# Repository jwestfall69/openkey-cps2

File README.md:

# openkey-cps2

* [Overview](#overview)
* [Project Status](#project-status)
* [Supported Games](#supported-games)
* [Hardware](#hardware)
   * [PCB Manufacturing](#pcb-manufacturing)
   * [BOM](#bom)
   * [Assembly](#assembly)
* [Programming](#programming)
  * [Hardware](#hardware-1)
  * [Software](#software)
  * [Testing](#testing)
* [Installation](#installation)
  * [93646B-3](#93646b-3)
  * [93646B-4](#93646b-4)
  * [93646B-5](#93646b-5)
  * [93646B-6](#93646b-6)
  * [93646B-7](#93646b-7)
  * [97691A-3 (all in one)](#97691a-3-all-in-one)
  * [97691A-4 (all in one)](#97691a-4-all-in-one)

## Overview
This is an opensource/hardware implementation of an on the fly CPS2 key programmer that consists of a board thats soldered onto the CPS2 B board or the CPS2 all-in-one boards.

**NOTE**: There is a typo on the silkscreen on hardware revision 2022-12-17.  The bypass cap is listed as being 100uf, when it should be 100nf.  This typo was fixed in hardware revision 2023-01-03, however the pictures below are all from the typo'd 2022-12-17 revision.

Individual boards:<br>

Panel:<br>

Details on *how* to program a CPS2 key data can be found in [Eduardo Cruz](http://arcadehacker.blogspot.com/)'s [write up](http://arcadehacker.blogspot.com/2016/09/capcom-cps2-security-programming-guide.html) and associated [firmware](https://github.com/ArcadeHacker/ArcadeHacker_CPS2).

Details on *what* to program can be found in MAME's [CPS2 driver](https://github.com/mamedev/mame/blob/master/src/mame/capcom/cps2.cpp) (the *.key files).

## Project Status
**PCB:** I would consider the design PCB done at this point.  I'm open to any input on changes/improvements as this is my first PCB design.

**Firmware:** Should be fulling working but more testing would be nice.  There are a lot of CPS2 games/keys.

**Documentation:** Work in progress

## Supported Games
**IMPORTANT**: You will want to program the ATtiny before soldering your game jumpers.  Specifically jumper #5 is also the programming pin on the ATtiny.  Jumping it will tie the pin to ground which will make programming impossible.

| Jumper<br>1234&nbsp;5678 | Program<br>ROM Labels | Mame<br>Rom Set | Game Names |
|:---------------:|:-------------|:------------|:-----------|
| 0000&nbsp;0000 | nffe | 1944 | 1944: The Loop Master (Euro 000620) |
| 0000 0001 | nffj | 1944j | 1944: The Loop Master (Japan 000620) |
| 0000 0010 | nffu | 1944u | 1944: The Loop Master (USA 000620) |
| 0000 0011 | 19xe | 19xx | 19XX: The War Against Destiny (Euro 960104) |
| 0000 0100 | 09xa<br>19xa | 19xxa<br>19xxar1 | 19XX: The War Against Destiny (Asia 960104)<br>19XX: The War Against Destiny (Asia 951207) |
| 0000 0101 | 19xb | 19xxb | 19XX: The War Against Destiny (Brazil 951218) |
| 0000 0110 | 19xh | 19xxh | 19XX: The War Against Destiny (Hispanic 951218) |
| 0000 0111 | 19xj-03b<br>19xj<br>19xj | 19xxj<br>19xxjr1<br>19xxjr2 | 19XX: The War Against Destiny (Japan 960104, yellow case)<br>19XX: The War Against Destiny (Japan 951225)<br>19XX: The War Against Destiny (Japan 951207) |
| 0000 1000 | 19xu | 19xxu | 19XX: The War Against Destiny (USA 951207) |
| 0000 1001 | pwge<br>pwge | armwar<br>armwarr1 | Armored Warriors (Euro 941024)<br>Armored Warriors (Euro 941011) |
| 0000 1010 | pwga<br>pwga | armwara<br>armwarar1 | Armored Warriors (Asia 941024)<br>Armored Warriors (Asia 940920) |
| 0000 1011 | pwgb | armwarb | Armored Warriors (Brazil 941024) |
| 0000 1100 | pwgu<br>pwgu | armwaru<br>armwaru1 | Armored Warriors (USA 941024)<br>Armored Warriors (USA 940920) |
| 0000 1101 | avpe | avsp | Alien vs. Predator (Euro 940520) |
| 0000 1110 | avpa | avspa | Alien vs. Predator (Asia 940520) |
| 0000 1111 | avph | avsph | Alien vs. Predator (Hispanic 940520) |
| 0001 0000 | avpj | avspj | Alien vs. Predator (Japan 940520) |
| 0001 0001 | avpu | avspu | Alien vs. Predator (USA 940520) |
| 0001 0010 | btce | batcir | Battle Circuit (Euro 970319) |
| 0001 0011 | btca | batcira | Battle Circuit (Asia 970319) |
| 0001 0100 | btcj | batcirj | Battle Circuit (Japan 970319) |
| 0001 0101 | tkoj | choko | Janpai Puzzle Choukou (Japan 010820) |
| 0001 0110 | csce<br>csce | csclub<br>csclub1 | Capcom Sports Club (Euro 971017)<br>Capcom Sports Club (Euro 970722) |
| 0001 0111 | csca | cscluba | Capcom Sports Club (Asia 970722) |
| 0001 1000 | csch | csclubh | Capcom Sports Club (Hispanic 970722) |
| 0001 1001 | cscj<br>cscj | csclubj<br>csclubjy | Capcom Sports Club (Japan 970722)<br>Capcom Sports Club (Japan 970722, yellow case) |
| 0001 1010 | cybe | cybots | Cyberbots: Fullmetal Madness (Euro 950424) |
| 0001 1011 | cybj | cybotsj | Cyberbots: Fullmetal Madness (Japan 950420) |
| 0001 1100 | cybu | cybotsu | Cyberbots: Fullmetal Madness (USA 950424) |
| 0001 1101 | dd2e<br>dd2e<br>dd2e<br>dd2e | ddsom<br>ddsomr1<br>ddsomr2<br>ddsomr3 | Dungeons & Dragons: Shadow over Mystara (Euro 960619)<br>Dungeons & Dragons: Shadow over Mystara (Euro 960223)<br>Dungeons & Dragons: Shadow over Mystara (Euro 960209)<br>Dungeons & Dragons: Shadow over Mystara (Euro 960208) |
| 0001 1110 | dd2a<br>dd2a | ddsoma<br>ddsomar1 | Dungeons & Dragons: Shadow over Mystara (Asia 960619)<br>Dungeons & Dragons: Shadow over Mystara (Asia 960208) |
| 0001 1111 | dd2b | ddsomb | Dungeons & Dragons: Shadow over Mystara (Brazil 960223) |
| 0010 0000 | dd2h | ddsomh | Dungeons & Dragons: Shadow over Mystara (Hispanic 960223) |
| 0010 0001 | dd2j<br>dd2j<br>dd2j | ddsomj<br>ddsomjr1<br>ddsomjr2 | Dungeons & Dragons: Shadow over Mystara (Japan 960619)<br>Dungeons & Dragons: Shadow over Mystara (Japan 960206)<br>Dungeons & Dragons: Shadow over Mystara (Japan 960223) |
| 0010 0010 | dd2u<br>dd2u | ddsomu<br>ddsomur1 | Dungeons & Dragons: Shadow over Mystara (USA 960619)<br>Dungeons & Dragons: Shadow over Mystara (USA 960209) |
| 0010 0011 | dade<br>dade | ddtod<br>ddtodr1 | Dungeons & Dragons: Tower of Doom (Euro 940412)<br>Dungeons & Dragons: Tower of Doom (Euro 940113) |
| 0010 0100 | dada<br>dada | ddtoda<br>ddtodar1 | Dungeons & Dragons: Tower of Doom (Asia 940412)<br>Dungeons & Dragons: Tower of Doom (Asia 940113) |
| 0010 0101 | dadh<br>dadh<br>dadh | ddtodh<br>ddtodhr1<br>ddtodhr2 | Dungeons & Dragons: Tower of Doom (Hispanic 940412)<br>Dungeons & Dragons: Tower of Doom (Hispanic 940125)<br>Dungeons & Dragons: Tower of Doom (Hispanic 940113) |
| 0010 0110 | dadj<br>dadj<br>dadj | ddtodj<br>ddtodjr1<br>ddtodjr2 | Dungeons & Dragons: Tower of Doom (Japan 940412)<br>Dungeons & Dragons: Tower of Doom (Japan 940125)<br>Dungeons & Dragons: Tower of Doom (Japan 940113) |
| 0010 0111 | dadu<br>dadu | ddtodu<br>ddtodur1 | Dungeons & Dragons: Tower of Doom (USA 940125)<br>Dungeons & Dragons: Tower of Doom (USA 940113) |
| 0010 1000 | gmde | dimahoo | Dimahoo (Euro 000121) |
| 0010 1001 | gmdu | dimahoou | Dimahoo (USA 000121) |
| 0010 1010 | vame | dstlk | Darkstalkers: The Night Warriors (Euro 940705) |
| 0010 1011 | vama | dstlka | Darkstalkers: The Night Warriors (Asia 940705) |
| 0010 1100 | vamh | dstlkh | Darkstalkers: The Night Warriors (Hispanic 940818) |
| 0010 1101 | vamu<br>vamu | dstlku<br>dstlkur1 | Darkstalkers: The Night Warriors (USA 940818)<br>Darkstalkers: The Night Warriors (USA 940705) |
| 0010 1110 | uece | ecofghtr | Eco Fighters (World 931203) |
| 0010 1111 | ueca | ecofghtra | Eco Fighters (Asia 931203) |
| 0011 0000 | uech | ecofghtrh | Eco Fighters (Hispanic 931203) |
| 0011 0001 | uecu<br>uecu | ecofghtru<br>ecofghtru1 | Eco Fighters (USA 940215)<br>Eco Fighters (USA 931203) |
| 0011 0010 | ggwu | gigawing | Giga Wing (USA 990222) |
| 0011 0011 | ggwa | gigawinga | Giga Wing (Asia 990222) |
| 0011 0100 | ggwb | gigawingb | Giga Wing (Brazil 990222) |
| 0011 0101 | ggwh | gigawingh | Giga Wing (Hispanic 990222) |
| 0011 0110 | ggwj | gigawingj | Giga Wing (Japan 990223) |
| 0011 0111 | gmdj | gmahou | Great Mahou Daisakusen (Japan 000121) |
| 0011 1000 | hs2u | hsf2 | Hyper Street Fighter II: The Anniversary Edition (USA 040202) |
| 0011 1001 | hs2a | hsf2a | Hyper Street Fighter II: The Anniversary Edition (Asia 040202) |
| 0011 1010 | hs2j<br>hs2j | hsf2j<br>hsf2j1<br>hsf2j2 | Hyper Street Fighter II: The Anniversary Edition (Japan 040202)<br>Street Fighter II: The Anniversary Edition (Japan 040123)<br>Hyper Street Fighter II: The Anniversary Edition (Japan 031222) |
| 0011 1011 | majj | jyangoku | Jyangokushi: Haoh no Saihai (Japan 990527) |
| 0011 1100 | rm2u | megaman2 | Mega Man 2: The Power Fighters (USA 960708) |
| 0011 1101 | rm2a | megaman2a | Mega Man 2: The Power Fighters (Asia 960708) |
| 0011 1110 | rm2h | megaman2h | Mega Man 2: The Power Fighters (Hispanic 960712) |
| 0011 1111 | rcmu<br>rcmu<br>rcmu | mmancp2u<br>mmancp2ur1<br>mmancp2ur2 | Mega Man: The Power Battle (CPS2, USA 951006, SAMPLE Version)<br>Mega Man: The Power Battle (CPS2, USA 950926, SAMPLE Version)<br>Mega Man: The Power Battle (CPS2, USA 950925, SAMPLE Version) |
| 0100 0000 | sys_rom1 | mmatrix | Mars Matrix: Hyper Solid Shooting (USA 000412) |
| 0100 0001 | mmxa | mmatrixa | Mars Matrix: Hyper Solid Shooting (Asia 000412) |
| 0100 0010 | mmxj | mmatrixj | Mars Matrix: Hyper Solid Shooting (Japan 000412) |
| 0100 0011 | mpne<br>mpn_03a<br>mpnj<br>mpne<br>mpnu | mpang<br>mpanga<br>mpangj<br>mpangr1<br>mpangu | Mighty! Pang (Euro 001010)<br>Mighty! Pang (Asia 001010)<br>Mighty! Pang (Japan 001011)<br>Mighty! Pang (Euro 000925)<br>Mighty! Pang (USA 001010) |
| 0100 0100 | mshe | msh | Marvel Super Heroes (Euro 951024) |
| 0100 0101 | msha | msha | Marvel Super Heroes (Asia 951024) |
| 0100 0110 | mshb<br>mshb | mshb<br>mshbr1 | Marvel Super Heroes (Brazil 951117)<br>Marvel Super Heroes (Brazil 951024) |
| 0100 0111 | mshh | mshh | Marvel Super Heroes (Hispanic 951117) |
| 0100 1000 | mshj<br>mshj | mshj<br>mshjr1 | Marvel Super Heroes (Japan 951117)<br>Marvel Super Heroes (Japan 951024) |
| 0100 1001 | mshu | mshu | Marvel Super Heroes (USA 951024) |
| 0100 1010 | mvse | mshvsf | Marvel Super Heroes Vs. Street Fighter (Euro 970625) |
| 0100 1011 | mvsa<br>mvsa | mshvsfa<br>mshvsfa1 | Marvel Super Heroes Vs. Street Fighter (Asia 970625)<br>Marvel Super Heroes Vs. Street Fighter (Asia 970620) |
| 0100 1100 | mvsb<br>mvsb | mshvsfb<br>mshvsfb1 | Marvel Super Heroes Vs. Street Fighter (Brazil 970827)<br>Marvel Super Heroes Vs. Street Fighter (Brazil 970625) |
| 0100 1101 | mvsh | mshvsfh | Marvel Super Heroes Vs. Street Fighter (Hispanic 970625) |
| 0100 1110 | mvsj<br>mvsj<br>mvsj | mshvsfj<br>mshvsfj1<br>mshvsfj2 | Marvel Super Heroes Vs. Street Fighter (Japan 970707)<br>Marvel Super Heroes Vs. Street Fighter (Japan 970702)<br>Marvel Super Heroes Vs. Street Fighter (Japan 970625) |
| 0100 1111 | mvsu<br>mvsu | mshvsfu<br>mshvsfu1 | Marvel Super Heroes Vs. Street Fighter (USA 970827)<br>Marvel Super Heroes Vs. Street Fighter (USA 970625) |
| 0101 0000 | mvce<br>mvce | mvsc<br>mvscr1 | Marvel Vs. Capcom: Clash of Super Heroes (Euro 980123)<br>Marvel Vs. Capcom: Clash of Super Heroes (Euro 980112) |
| 0101 0001 | mvca<br>mvca | mvsca<br>mvscar1 | Marvel Vs. Capcom: Clash of Super Heroes (Asia 980123)<br>Marvel Vs. Capcom: Clash of Super Heroes (Asia 980112) |
| 0101 0010 | mvcb | mvscb | Marvel Vs. Capcom: Clash of Super Heroes (Brazil 980123) |
| 0101 0011 | mvch | mvsch | Marvel Vs. Capcom: Clash of Super Heroes (Hispanic 980123) |
| 0101 0100 | mvcj<br>mvcj<br>mvc_ja | mvscj<br>mvscjr1<br>mvscjsing | Marvel Vs. Capcom: Clash of Super Heroes (Japan 980123)<br>Marvel Vs. Capcom: Clash of Super Heroes (Japan 980112)<br>Marvel Vs. Capcom: Clash of Super Heroes (Japan 980123) (Single PCB) |
| 0101 0101 | mvcu<br>mvcu | mvscu<br>mvscur1 | Marvel Vs. Capcom: Clash of Super Heroes (USA 980123)<br>Marvel Vs. Capcom: Clash of Super Heroes (USA 971222) |
| 0101 0110 | vphe | nwarr | Night Warriors: Darkstalkers' Revenge (Euro 950316) |
| 0101 0111 | vpha | nwarra | Night Warriors: Darkstalkers' Revenge (Asia 950302) |
| 0101 1000 | vphb | nwarrb | Night Warriors: Darkstalkers' Revenge (Brazil 950403) |
| 0101 1001 | vphh | nwarrh | Night Warriors: Darkstalkers' Revenge (Hispanic 950403) |
| 0101 1010 | vphu | nwarru | Night Warriors: Darkstalkers' Revenge (USA 950406) |
| 0101 1011 | pcfj | pfghtj | Pocket Fighter (Japan 970904) |
| 0101 1100 | pwgj<br>pwgj | pgear<br>pgearr1 | Powered Gear: Strategic Variant Armor Equipment (Japan 941024)<br>Powered Gear: Strategic Variant Armor Equipment (Japan 940916) |
| 0101 1101 | pgau | progear | Progear (USA 010117) |
| 0101 1110 | pgaa | progeara | Progear (Asia 010117) |
| 0101 1111 | pgaj | progearj | Progear no Arashi (Japan 010117) |
| 0110 0000 | pl2e<br>pl2j<br>pl2j | pzloop2<br>pzloop2j<br>pzloop2jr1 | Puzz Loop 2 (Euro 010302)<br>Puzz Loop 2 (Japan 010226)<br>Puzz Loop 2 (Japan 010205) |
| 0110 0001 | tqzj | qndream | Quiz Nanairo Dreams: Nijiirochou no Kiseki (Japan 96086) |
| 0110 0010 | smbe | ringdest | Ring of Destruction: Slammasters II (Euro 940902) |
| 0110 0011 | smba | ringdesta | Ring of Destruction: Slammasters II (Asia 940831) |
| 0110 0100 | smbb<br>smbh | ringdestb<br>ringdesth | Ring of Destruction: Slammasters II (Brazil 940902)<br>Ring of Destruction: Slammasters II (Hispanic 940902) |
| 0110 0101 | rcmj | rmancp2j | Rockman: The Power Battle (CPS2, Japan 950922) |
| 0110 0110 | rm2j | rockman2j | Rockman 2: The Power Fighters (Japan 960708) |
| 0110 0111 | sfze<br>sfze<br>sfze<br>sfze | sfa<br>sfar1<br>sfar2<br>sfar3 | Street Fighter Alpha: Warriors' Dreams (Euro 950727)<br>Street Fighter Alpha: Warriors' Dreams (Euro 950718)<br>Street Fighter Alpha: Warriors' Dreams (Euro 950627)<br>Street Fighter Alpha: Warriors' Dreams (Euro 950605) |
| 0110 1000 | sz2e | sfa2 | Street Fighter Alpha 2 (Euro 960229) |
| 0110 1001 | sz2u<br>sz2u | sfa2u<br>sfa2ur1 | Street Fighter Alpha 2 (USA 960430)<br>Street Fighter Alpha 2 (USA 960306) |
| 0110 1010 | sz3e | sfa3 | Street Fighter Alpha 3 (Euro 980904) |
| 0110 1011 | sz3b | sfa3b | Street Fighter Alpha 3 (Brazil 980629) |
| 0110 1100 | sz3h<br>sz3h | sfa3h<br>sfa3hr1 | Street Fighter Alpha 3 (Hispanic 980904)<br>Street Fighter Alpha 3 (Hispanic 980629) |
| 0110 1101 | sz3u<br>sz3u<br>sz3-usam_03 | sfa3u<br>sfa3ur1<br>sfa3us | Street Fighter Alpha 3 (USA 980904)<br>Street Fighter Alpha 3 (USA 980629)<br>Street Fighter Alpha 3 (USA 980616, SAMPLE Version) |
| 0110 1110 | sfzu | sfau | Street Fighter Alpha: Warriors' Dreams (USA 950627) |
| 0110 1111 | sz2a | sfz2a | Street Fighter Zero 2 (Asia 960227) |
| 0111 0000 | szaa<br>szaa | sfz2al<br>sfz2alr1 | Street Fighter Zero 2 Alpha (Asia 960826)<br>Street Fighter Zero 2 Alpha (Asia 960805) |
| 0111 0001 | szab | sfz2alb | Street Fighter Zero 2 Alpha (Brazil 960813) |
| 0111 0010 | szah | sfz2alh | Street Fighter Zero 2 Alpha (Hispanic 960813) |
| 0111 0011 | szaj | sfz2alj | Street Fighter Zero 2 Alpha (Japan 960805) |
| 0111 0100 | sz2b<br>sz2b | sfz2b<br>sfz2br1 | Street Fighter Zero 2 (Brazil 960531)<br>Street Fighter Zero 2 (Brazil 960304) |
| 0111 0101 | sz2h | sfz2h | Street Fighter Zero 2 (Hispanic 960304) |
| 0111 0110 | sz2j<br>sz2j | sfz2j<br>sfz2jr1 | Street Fighter Zero 2 (Japan 960430)<br>Street Fighter Zero 2 (Japan 960227) |
| 0111 0111 | sz2n | sfz2n | Street Fighter Zero 2 (Oceania 960229) |
| 0111 1000 | sz3a<br>sz3a | sfz3a<br>sfz3ar1 | Street Fighter Zero 3 (Asia 980904)<br>Street Fighter Zero 3 (Asia 980701) |
| 0111 1001 | sz3j<br>sz3j<br>sz3j | sfz3j<br>sfz3jr1<br>sfz3jr2 | Street Fighter Zero 3 (Japan 980904)<br>Street Fighter Zero 3 (Japan 980727)<br>Street Fighter Zero 3 (Japan 980629) |
| 0111 1010 | sfza<br>sfza | sfza<br>sfzar1 | Street Fighter Zero (Asia 950627)<br>Street Fighter Zero (Asia 950605) |
| 0111 1011 | sfzb<br>sfzb | sfzb<br>sfzbr1 | Street Fighter Zero (Brazil 951109)<br>Street Fighter Zero (Brazil 950727) |
| 0111 1100 | sfzh<br>sfzh | sfzh<br>sfzhr1 | Street Fighter Zero (Hispanic 950718)<br>Street Fighter Zero (Hispanic 950627) |
| 0111 1101 | sfzj<br>sfzj<br>sfzj | sfzj<br>sfzjr1<br>sfzjr2 | Street Fighter Zero (Japan 950727)<br>Street Fighter Zero (Japan 950627)<br>Street Fighter Zero (Japan 950605) |
| 0111 1110 | pcfu | sgemf | Super Gem Fighter Mini Mix (USA 970904) |
| 0111 1111 | pcfa | sgemfa | Super Gem Fighter: Mini Mix (Asia 970904) |
| 1000 0000 | pcfh | sgemfh | Super Gem Fighter: Mini Mix (Hispanic 970904) |
| 1000 0001 | smbj<br>smbj | smbomb<br>smbombr1 | Super Muscle Bomber: The International Blowout (Japan 940831)<br>Super Muscle Bomber: The International Blowout (Japan 940808) |
| 1000 0010 | pzfe | spf2t | Super Puzzle Fighter II Turbo (Euro 960529) |
| 1000 0011 | pzfa | spf2ta | Super Puzzle Fighter II Turbo (Asia 960529) |
| 1000 0100 | pzfh | spf2th | Super Puzzle Fighter II Turbo (Hispanic 960531) |
| 1000 0101 | pzfu | spf2tu | Super Puzzle Fighter II Turbo (USA 960620) |
| 1000 0110 | pzfj | spf2xj | Super Puzzle Fighter II X (Japan 960531) |
| 1000 0111 | ssfe<br>ssfe | ssf2<br>ssf2r1 | Super Street Fighter II: The New Challengers (World 931005)<br>Super Street Fighter II: The New Challengers (World 930911) |
| 1000 1000 | ssfa<br>ssfa | ssf2a<br>ssf2ar1 | Super Street Fighter II: The New Challengers (Asia 931005)<br>Super Street Fighter II: The New Challengers (Asia 930914) |
| 1000 1001 | ssfh | ssf2h | Super Street Fighter II: The New Challengers (Hispanic 930911) |
| 1000 1010 | ssfj<br>ssfj<br>ssfj | ssf2j<br>ssf2jr1<br>ssf2jr2 | Super Street Fighter II: The New Challengers (Japan 931005)<br>Super Street Fighter II: The New Challengers (Japan 930911)<br>Super Street Fighter II: The New Challengers (Japan 930910) |
| 1000 1011 | ssfh | ssf2t | Super Street Fighter II Turbo (World 940223) |
| 1000 1100 | sfxa | ssf2ta | Super Street Fighter II Turbo (Asia 940223) |
| 1000 1101 | ssfe<br>ssfe | ssf2tb<br>ssf2tbr1 | Super Street Fighter II: The Tournament Battle (World 931119)<br>Super Street Fighter II: The Tournament Battle (World 930911) |
| 1000 1110 | ssfa | ssf2tba | Super Street Fighter II: The Tournament Battle (Asia 931005) |
| 1001 0000 | ssftj<br>ssfj | ssf2tbj<br>ssf2tbj1 | Super Street Fighter II: The Tournament Battle (Japan 931005)<br>Super Street Fighter II: The Tournament Battle (Japan 930911) |
| 1001 0001 | ssfu | ssf2tbu | Super Street Fighter II: The Tournament Battle (USA 930911) |
| 1001 0010 | sfxh | ssf2th | Super Street Fighter II Turbo (Hispanic 940223) |
| 1001 0011 | sfxu<br>sfxu | ssf2tu<br>ssf2tur1 | Super Street Fighter II Turbo (USA 940323)<br>Super Street Fighter II Turbo (USA 940223) |
| 1001 0100 | ssfu<br>ssfu | ssf2u<br>ssf2us2 | Super Street Fighter II: The New Challengers (USA 930911)<br> |
| 1001 0101 | sfxj<br>sfxj | ssf2xj<br>ssf2xjr1 | Super Street Fighter II X: Grand Master Challenge (Japan 940311)<br>Super Street Fighter II X: Grand Master Challenge (Japan 940223) |
| 1001 0110 | sfxo | ssf2xjr1r | Super Street Fighter II X: Grand Master Challenge (Japan 940223 rent version) |
| 1001 0111 | uecj | uecology | Ultimate Ecology (Japan 931203) |
| 1001 1000 | vamj<br>vamj<br>vamj | vampj<br>vampja<br>vampjr1 | Vampire: The Night Warriors (Japan 940705)<br>Vampire: The Night Warriors (Japan 940705 alt)<br>Vampire: The Night Warriors (Japan 940630) |
| 1001 1001 | vh2j<br>vh2j | vhunt2<br>vhunt2r1 | Vampire Hunter 2: Darkstalkers Revenge (Japan 970929)<br>Vampire Hunter 2: Darkstalkers Revenge (Japan 970913) |
| 1001 1010 | vphj<br>vphj<br>vphjstop<br>vphj | vhuntj<br>vhuntjr1<br>vhuntjr1s<br>vhuntjr2 | Vampire Hunter: Darkstalkers' Revenge (Japan 950316)<br>Vampire Hunter: Darkstalkers' Revenge (Japan 950307)<br>Vampire Hunter: Darkstalkers' Revenge (Japan 950307 stop version)<br>Vampire Hunter: Darkstalkers' Revenge (Japan 950302) |
| 1001 1011 | vm3e | vsav | Vampire Savior: The Lord of Vampire (Euro 970519) |
| 1001 1100 | vs2j | vsav2 | Vampire Savior 2: The Lord of Vampire (Japan 970913) |
| 1001 1101 | vm3a | vsava | Vampire Savior: The Lord of Vampire (Asia 970519) |
| 1001 1110 | vm3b | vsavb | Vampire Savior: The Lord of Vampire (Brazil 970519) |
| 1001 1111 | vm3h | vsavh | Vampire Savior: The Lord of Vampire (Hispanic 970519) |
| 1010 0000 | vm3j | vsavj | Vampire Savior: The Lord of Vampire (Japan 970519) |
| 1010 0001 | vm3u | vsavu | Vampire Savior: The Lord of Vampire (USA 970519) |
| 1010 0010 | xmne<br>xmne | xmcota<br>xmcotar1 | X-Men: Children of the Atom (Euro 950331)<br>X-Men: Children of the Atom (Euro 950105) |
| 1010 0011 | xmna<br>xmna<br>xmna | xmcotaa<br>xmcotaar1<br>xmcotaar2 | X-Men: Children of the Atom (Asia 950105)<br>X-Men: Children of the Atom (Asia 941219)<br>X-Men: Children of the Atom (Asia 941217) |
| 1010 0100 | xmnb | xmcotab | X-Men: Children of the Atom (Brazil 950331) |
| 1010 0101 | xmnh<br>xmnh | xmcotah<br>xmcotahr1 | X-Men: Children of the Atom (Hispanic 950331)<br>X-Men: Children of the Atom (Hispanic 950105) |
| 1010 0110 | xmnj<br>xmnj<br>xmnj<br>xmnj<br>xmno | xmcotaj<br>xmcotaj1<br>xmcotaj2<br>xmcotaj3<br>xmcotajr | X-Men: Children of the Atom (Japan 950105)<br>X-Men: Children of the Atom (Japan 941222)<br>X-Men: Children of the Atom (Japan 941219)<br>X-Men: Children of the Atom (Japan 941217)<br>X-Men: Children of the Atom (Japan 941208 rent version) |
| 1010 0111 | xmnu | xmcotau | X-Men: Children of the Atom (USA 950105) |
| 1010 1000 | xvse<br>xvse | xmvsf<br>xmvsfr1 | X-Men Vs. Street Fighter (Euro 961004)<br>X-Men Vs. Street Fighter (Euro 960910) |
| 1010 1001 | xvsa<br>xvsa<br>xvsa<br>xvsa | xmvsfa<br>xmvsfar1<br>xmvsfar2<br>xmvsfar3 | X-Men Vs. Street Fighter (Asia 961023)<br>X-Men Vs. Street Fighter (Asia 961004)<br>X-Men Vs. Street Fighter (Asia 960919)<br>X-Men Vs. Street Fighter (Asia 960910) |
| 1010 1010 | xvsb | xmvsfb | X-Men Vs. Street Fighter (Brazil 961023) |
| 1010 1011 | xvsh | xmvsfh | X-Men Vs. Street Fighter (Hispanic 961004) |
| 1010 1100 | xvsj<br>xvsj<br>xvsj<br>xvsj | xmvsfj<br>xmvsfjr1<br>xmvsfjr2<br>xmvsfjr3<br>xmvsfjr4 | X-Men Vs. Street Fighter (Japan 970113)<br>X-Men Vs. Street Fighter (Japan 961023)<br>X-Men Vs. Street Fighter (Japan 961004)<br>X-Men Vs. Street Fighter (Japan 960910)<br>X-Men Vs. Street Fighter (Japan 960909) |
| 1010 1101 | xvsu<br>xvsu<br>xvsu | xmvsfu<br>xmvsfur1<br>xmvsfur2 | X-Men Vs. Street Fighter (USA 961023)<br>X-Men Vs. Street Fighter (USA 961004)<br>X-Men Vs. Street Fighter (USA 960910) |
| 1010 1110 | | | Phoenix Key (0xff filled) |

## Hardware
### PCB Manufacturing
For thickness I've been using 1mm, but standard 1.6mm will work fine too.

The board has 2 sets of castellated holes (through holes cut in half on the edge of the board).  When ordering make sure you pick the option for castellated holes as they require special processing.  If you don't pick the option, your castellated holes will likely be mangled and look like this

**Mangled Castellated Holes**<br>

I've been using [jlcpcb](https://jlcpcb.com/) for PCB manufacturing.  For them, picking castellated holes adds around a $40 fee to the order.  They also seem to have an unwritten limit of 30 PCBs per order that have castellated holes.  If you go above this they may reject your order or ask you if its ok to remove the castellated holes option (don't do it!).

If you want more then 30 PCBs or want them assembled you will want to use the
panel version of openkey-cps2.  More detail regarding this can be found in [PANEL.md](PANEL.md).

### BOM
| Description | Part Number | DigiKey | Mouser | Notes |
|-------------|-------------|---------|--------|-------|
| ATtiny404 20Mhz | ATTINY404-SSN | [ATTINY404-SSN-ND](https://www.digikey.com/en/products/detail/microchip-technology/ATTINY404-SSN/9947546) | [556-ATTINY404-SSNR](https://www.mouser.com/ProductDetail/Microchip-Technology-Atmel/ATTINY404-SSNR?qs=F5EMLAvA7IAEqD7Aw0z%252B9Q%3D%3D) | Other ATtiny tinyAVR 0/1/2-series models should be viable as well.  The code compiles to a little over 3K in size, so any that have 4K or more of flash should work.  Just note I have only tested with 404s |
| 100nf / 0.1uf SMD Ceramic Capacitor 0805 Size | | | | |

### Assembly
Nothing special here just install the ATtiny and the bypass cap.

**IMPORTANT**: You will want to program the ATtiny before soldering your game jumpers.  Specifically jumper #5 is also the programming pin on the ATtiny.  Jumping it will tie the pin to ground which will make programming impossible.

## Programming
### Hardware
Programming is done with a UPDI programmer.  I've been using this one:

[Serial UPDI Programmer for ATmega 0-Series, or ATtiny 0-Series or 1-Series, or AVR DA or AVR DB](https://www.amazon.com/dp/B09X64YRLD?psc=1&ref=ppx_yo2ov_dt_b_product_details)

Note: This programmer (and likely others) has a switch for 3.3V and 5V.  Set it to 5V.

The openkey-cps2 programming port consists of 3x pads (VCC, GND, UPDI) that will need to be connected to the programmer.  I've been using a short 3 pin female to female IDC cable with [pogo pins](https://www.amazon.com/dp/B00X7C8PGE?psc=1&ref=ppx_yo2ov_dt_b_product_details) on one end to do this.  Additionally you could probably use something like [this](https://www.amazon.com/dp/B09MGG4C6X?ref=ppx_yo2ov_dt_b_product_details&th=1) if you are going to be programming a bunch.

Of course be sure you properly orient the board so the labeled pads match up.  vcc to vcc, gnd to gnd, and updi to updi.

### Software
For software I've been using the [Arduino IDE](https://www.arduino.cc/en/software/OldSoftwareReleases) with [megaTinyCore](https://github.com/SpenceKonde/megaTinyCore), which adds support for tinyAVR 0/1/2-Series MCUs.

**NOTE**: The makers of megaTinyCore currently recommend using Arduino IDE version 1.8.13 for best compatibility.
 2.0 definitely does not work!

To install the megaTinyCore you, should just need to add http://drazzy.com/package_drazzy.com_index.json to "Addit
ional Boards Manager URLs" in the settings for the Arduino IDE.

From there you need to configure the board/programming settings.  I've been using these:

### Testing
If you are selling or giving away the openkey-cps2's that you have assembled/programmed its nice to be able to test them first.  This section explains how you can test the board without having to install it.

You will need to get your hands on a "1944: The Loop Master (Euro 000620)" in a 93646B-6 or 93646B-7 B board.  For mine I just made a conversion using the 1944 mame romset.  This specific game is needed because its game jumper 0000 0000.

Additionally you will need to create the following cable

Side A:<br>

Side B:<br>

I would advise making this cable about 24 inches long.

You will note that side "A" is 6 pin female connectors, which break out into a 5 pin female connector and 3 pin female connector "B" side.  The "B" side then has pogo pins installed with super glue to keep them steady.  Additionally on the 3 pin female connector "B" side, pins 2 and 3 are just connected to each other.

The red wire is +5V, black wire is GND, remaining are data lines.

The "A" side 6 pin connector should be plugged into CN9 on the B board, with +5V on pin 1, and GND on pin 6 as shown.

**IMPORTANT**: The +5V on the 3 pin female/pogo pin connector will be live when you power on the board, so be extra careful you don't touch anything with it or it could cause a short/damage.

CPS2 boards will hold onto the programmed key data for a while after they have been powered off.  So to properly test the openkey-cps2 its best to program the wrong key, verify it breaks the game, then program the correct key to verify it works.

**Programming the WRONG key**
1. Power on the CPS2 board
2. Connect the 5 pogo pin connector to pins 2-6 of CN9 on the openkey-cps2
3. Connect the 3 pogo pin connector to the UPDI header on openkey-cps2, with the red wire connected to VCC pad, and the pins 2-3 connected to GND and UPDI pads

This should result is a solid color screen, mine is normally purple.

The UPDI pad on the UPDI header is shared with jumper #5 of the game select.  By jumping the GND and UPDI pads together its cause the MCU to program game 0000 1000 or 19XX: The War Against Destiny (USA 951207), which is the wrong key for 1944: The Loop Master (Euro 000620)

**Programming the CORRECT key**
1. Remove both the 5 pogo pin and 3 pogo pin connectors from the openkey-cps2 board
2. Connect the 5 pogo pin connector to pins 2-6 of CN9 on the openkey-cps2
3. Using the 3 pogo pin connector, only connect the red wire pogo pin to the VCC pad on the UPDI header.  Do not connect anything to the GND and UPDI pads

By only applying +5V on the VCC pad on UPDI header and NOT jumping the GND/UPDI pads it will cause the MCU to program game 0000 0000.

The game should boot a few seconds later

You do not need to power off the CPS2 board in between programming the wrong/correct key or even between testing multiple openkey-cps2 board.  Part of the programming process will reset the game.

## Installation
Below are pictures for installing openkey-cps2 on the different cps2 board revisions.  

You will notice there are 3 boxes on the board, 2 with solder pads (+5V and GND), and 1 jumper.  Within the box is a short hand version of which board revisions need which of them.

  * +5V has **B-345** which means its needed for revisions 93646**B-3**, 93646**B-4**, and 93646**B-5**
  * JUMP has **B-67** and **A-34** which means it needs to be jumped for revisions 93646**B-6**, 93646**B-7**, 97691**A-3** and 97691**A-4**
  * GND has **B-34** which means its needed for revisions 93646**B-3** and 93646**B-4**

### **93646B-3**
### **93646B-4**
---
93646B-3 and 93646B-4 have the same install process.

Identify CN2 on the top side of the CPS2 B Board PCB.  This is where openkey-cps2 will be installed.

Your board will likely have the resistor shown in the below picture.

Temporarily desolder the top connection of the resistor, move it out of the way and install openkey-cps2 as shown below.  Additionally make note of the red and green arrows/lines as these will be the locations we wire up for +5V and GND.

Re-solder the resistor and wire up the +5V and GND wires as shown below.  Then jumper 1 to 8 based on which game you need. 

### **93646B-5**
---
NOTE: I don't have a 93646B-5, but this is what should be required for the installation.

Identify CN9 on the top side of the CPS2 B Board PCB.  The underside of CN9 is what we will be installing openkey-cps2 to.

Top:

Bottom:

Solder the castellated holes on CN9 of openkey-cps2 to the underside pins for CN9 on the CPS2 PCB.  Additionally solder a wire going from the +5V pad on the openkey-cps2 to RA2 pin 1 as seen below.  Then jumper 1 to 8 based on which game you need.  

Installed:

### **93646B-6**
### **93646B-7**
---
93646B-6 and 93646B-7 have the same install process.

Identify CN9 on the top side of the CPS2 B Board PCB.  The underside of CN9 is what we will be installing openkey-cps2 to.

Top:

Bottom:

Solder the castellated holes on CN9 of openkey-cps2 to the underside pins for CN9 on the CPS2 PCB.  Additionally jumper the **JUMP** pad as pointed out by the green arrow in the picture below.  Then jumper 1 to 8 based on which game you need.  

Installed

### **97691A-3 (all in one)**
### **97691A-4 (all in one)**
---
97691A-3 and 97691A-4 have the same install process.

Identify CN1 on the top side of the CPS2 PCB.  It should be next to the memory socket in the corner.  The underside of CN1 is what we will be installing openkey-cps2 to.

Top:

Bottom:

openkey-cps2 will sit on top of those 4 resistors seen in the above picture.  Solder the castellated holes on CN9 of openkey-cps2 to the underside pins for CN1 on the CPS2 PCB.  Additionally jumper the **JUMP** pad as pointed out by the green arrow in the picture below.  Then jumper 1 to 8 based on which game you need.  

Installed:

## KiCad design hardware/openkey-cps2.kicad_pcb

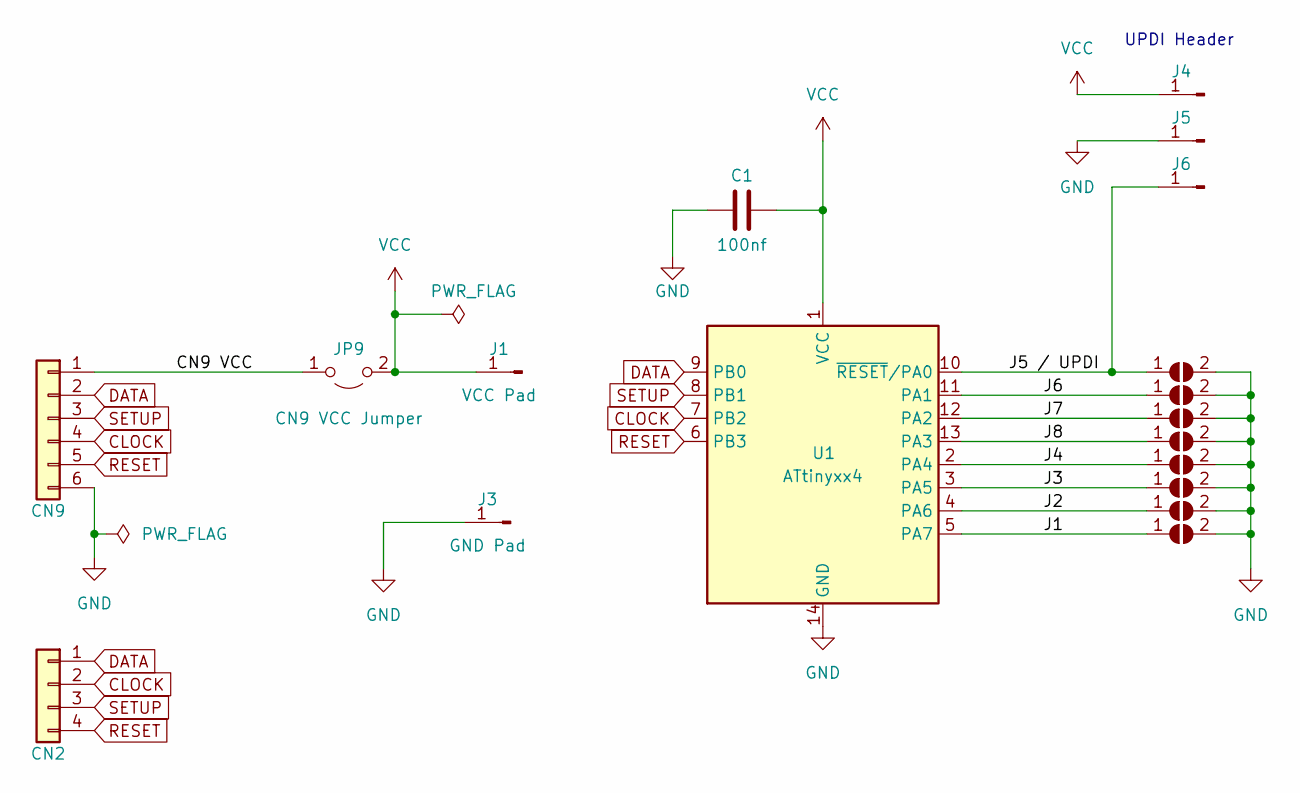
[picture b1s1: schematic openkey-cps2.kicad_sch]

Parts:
C1: 100nf; C_0805_2012Metric_Pad1.18x1.45mm_HandSolder; LCSC C49678
CN9: Conn_01x06; PinHeader_1x06_P2.54mm_Vertical
J1: VCC Pad; TestPoint_Pad_D2.5mm
J2: CN2; PinHeader_1x04_P2.54mm_Vertical
J3: GND Pad; TestPoint_Pad_D2.5mm
J4: VCC; TestPoint_Pad_D1.5mm
J5: GND; TestPoint_Pad_D1.5mm
J6: J5 / UDPI; TestPoint_Pad_D1.5mm
JP1, JP2, JP3, JP4, JP5, JP6, JP7, JP8: SolderJumper_2_Open; SolderJumper-2_P1.3mm_Open_RoundedPad1.0x1.5mm
JP9: CN9 VCC Jumper; SolderJumper-2_P1.3mm_Open_RoundedPad1.0x1.5mm
U1: ATtinyxx4; SOIC-14_3.9x8.7mm_P1.27mm; LCSC C1339119

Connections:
/CN9 VCC: CN9.1, JP9.1 (A)
/J1: JP8.1 (A), U1.5 (PA7)
/J2: JP7.1 (A), U1.4 (PA6)
/J3: JP6.1 (A), U1.3 (PA5)
/J4: JP5.1 (A), U1.2 (PA4)
/J5 / UPDI: J6.1 (Pin_1_1), JP1.1 (A), U1.10 (~RESET/PA0)
/J6: JP2.1 (A), U1.11 (PA1)
/J7: JP3.1 (A), U1.12 (PA2)
/J8: JP4.1 (A), U1.13 (PA3)
CLOCK: CN9.4, J2.2, U1.7 (PB2)
DATA: CN9.2, J2.1, U1.9 (PB0)
GND: C1.1, CN9.6, J3.1 (Pin_1_1), J5.1 (Pin_1_1), JP1.2 (B), JP2.2 (B), JP3.2 (B), JP4.2 (B), JP5.2 (B), JP6.2 (B), JP7.2 (B), JP8.2 (B), U1.14 (GND)
RESET: CN9.5, J2.4, U1.6 (PB3)
SETUP: CN9.3, J2.3, U1.8 (PB1)
VCC: C1.2, J1.1 (Pin_1_1), J4.1 (Pin_1_1), JP9.2 (B), U1.1 (VCC)

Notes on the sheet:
UPDI Header

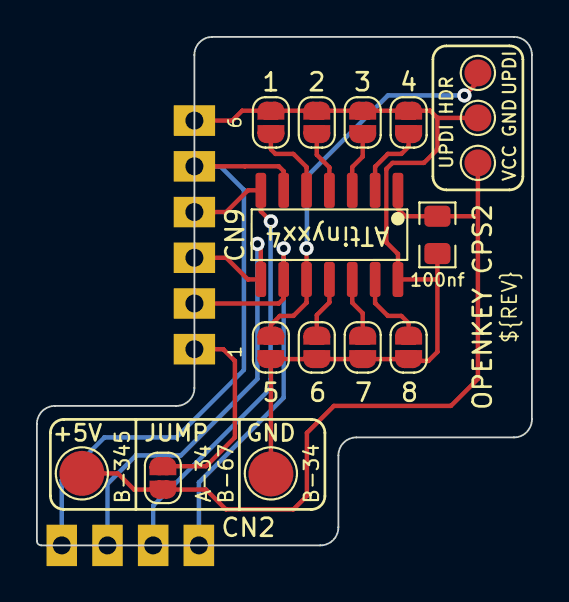
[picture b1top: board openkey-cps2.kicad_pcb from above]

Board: 2 copper layers, 27.5 x 28.2 mm, 18 parts (0 on the bottom side), 15 nets.

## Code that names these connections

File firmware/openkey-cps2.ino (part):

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  }
}

// JP1 = PA7 = bit7
// JP2 = PA6 = bit6
// JP3 = PA5 = bit5
// JP4 = PA6 = bit4
// JP5 = PA0 = bit3
// JP6 = PA1 = bit2
// JP7 = PA2 = bit1
// JP8 = PA3 = bit0
uint8_t read_jumpers() {
  uint8_t jumpers = 0;
  uint8_t raw;
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
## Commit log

2022-10-12 initial checkin
2022-10-12 Add openkey-kicad-library as submodule
2022-10-12 Initial check of board/firmware
2022-10-12 Move firmware to openkey-cps2 sub dir to keep arduino ide happy
2022-10-12 Set output path for gerber files, other minor tweaks
2022-10-12 Add gerber export directories to .gitignore
2022-10-27 Some minor tweaks around the vcc jumper and pad
    Should make it more obvious what is for what
2022-10-27 bump rev number
2022-11-13 Initial support for 93646B-3/4 revision boards
2022-11-14 Docs: Add supported games table
    While doing an audit of the firmware for missing keys, I went ahead and
    auto generated the supported games table.
2022-11-25 HW: Add support for 93646B-3/4 and 97691A-3/4. Add UPDI header.
2022-11-26 HW: adjust a couple traces
2022-11-27 HW: get most everything 0.25mm aligned
2022-12-08 HW: tweak so a VCC trace isn't so close to edge
2022-12-17 HW: somehow missed connecting the ground pad, doh
2022-12-29 Add panel
2022-12-29 Add docs
2022-12-29 Remove unneeded picture
2022-12-30 Doc updates
    - remove tested column from supported games
    - remove some horizontal lines since github's markdown auto adds them
    for some headers
2022-12-30 Docs: tweak jumper column in table
    Hopefully fix the formatting
2023-01-04 HW: bypass cap value typo'd as 100uf when it should be 100nf
    Thanks for hatmoose for pointing out the typo
2023-01-12 Docs: Add comment about the typo'd bypass cap value in the pics
2023-01-15 Docs: Add testing section
2023-01-15 Docs: additional info around castellated holes
    thanks to hatmoose for the picture
2023-10-14 Increase startup delay
    User Tailsnic reported that openkey wasn't programming
    on one of his cabinets (powersupply issue?). Through
    some testing he found if he increased the start up delay
    (arduino ide) and the initial delay() in the code it
    started working.
    Since programming holds the board in reset, inceasing
2026-05-20 panel + assembly updates
    - have kikit create the panel (was done by hand before)
    - have jlcpcb fabrication plugin create bom/positions files for the panel
    - create PANEL.md with instructions for having jlcpcb assemble the board
    - update kicad files to 10.x
